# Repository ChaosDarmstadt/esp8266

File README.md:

Fun projects with ESP8266 IoT chip

## ESPLight

ESP8266 and WS2812 based, wifi enabled LED matrix.
What you need:

* 3.3V LDO TLV2217-33KCSE3
* 22uF Elko
* 0.1uF
* 5V 4A with barrel connector
* 5,5/2,5 mm barrel
* WS2812 rgb LED 60 px/m
* spacer bolt + screws M3 10mm
* 6x Push Button
* 10k resistor 1/4W
* ESP8266 ESP-07
* Stuff for manufacturing the PCB
* 2x 12cm x 26cm x 3mm translucent acrylic glass
* 3.3V TTL FTDI for flashing NodeMCU and nodemcu uploader for lua scripts

(AliExpress, Bauhaus, Pollin)

### related links
[send text over wifi](https://github.com/Nervengift/esplight.py)
[nodemcu](https://github.com/nodemcu/nodemcu-firmware)
[basic howto](https://wiki.chaos-darmstadt.de/wiki/ESP8266)

## ESPBreakout
ESP8266 Breakout Board

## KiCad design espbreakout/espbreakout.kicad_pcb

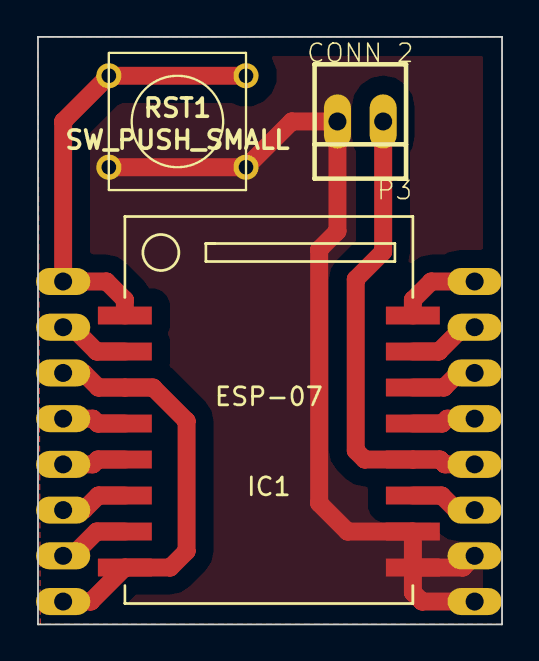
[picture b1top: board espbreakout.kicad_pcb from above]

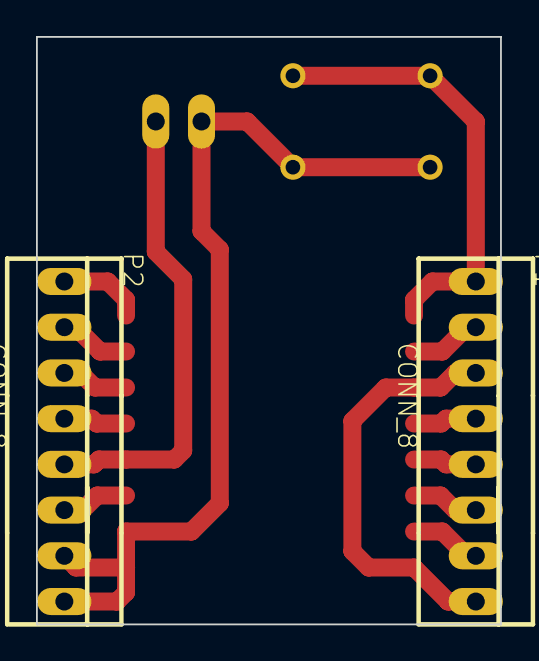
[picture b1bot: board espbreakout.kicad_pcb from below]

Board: 2 copper layers, 25.8 x 32.6 mm, 5 parts (2 on the bottom side), 14 nets.

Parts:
IC1: ESP-07; ESP-07v2
P1, P2: CONN_8; PINHEAD1-8
P3: CONN_2; PINHEAD1-2
RST1: SW_PUSH_SMALL

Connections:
+3.3V: IC1.3, IC1.8, P1.3, P1.8
GND: IC1.9, IC1.10, P2.7, P2.8, P3.2, RST1.2
unnamed: IC1.11, P2.6
unnamed: IC1.13, P2.4
unnamed: IC1.14, P2.3
unnamed: IC1.15, P2.2
unnamed: IC1.16, P2.1
unnamed: IC1.1, P1.1, RST1.1
unnamed: IC1.2, P1.2
unnamed: IC1.4, P1.4
unnamed: IC1.5, P1.5
unnamed: IC1.6, P1.6
unnamed: IC1.7, P1.7
unnamed: IC1.12, P2.5, P3.1

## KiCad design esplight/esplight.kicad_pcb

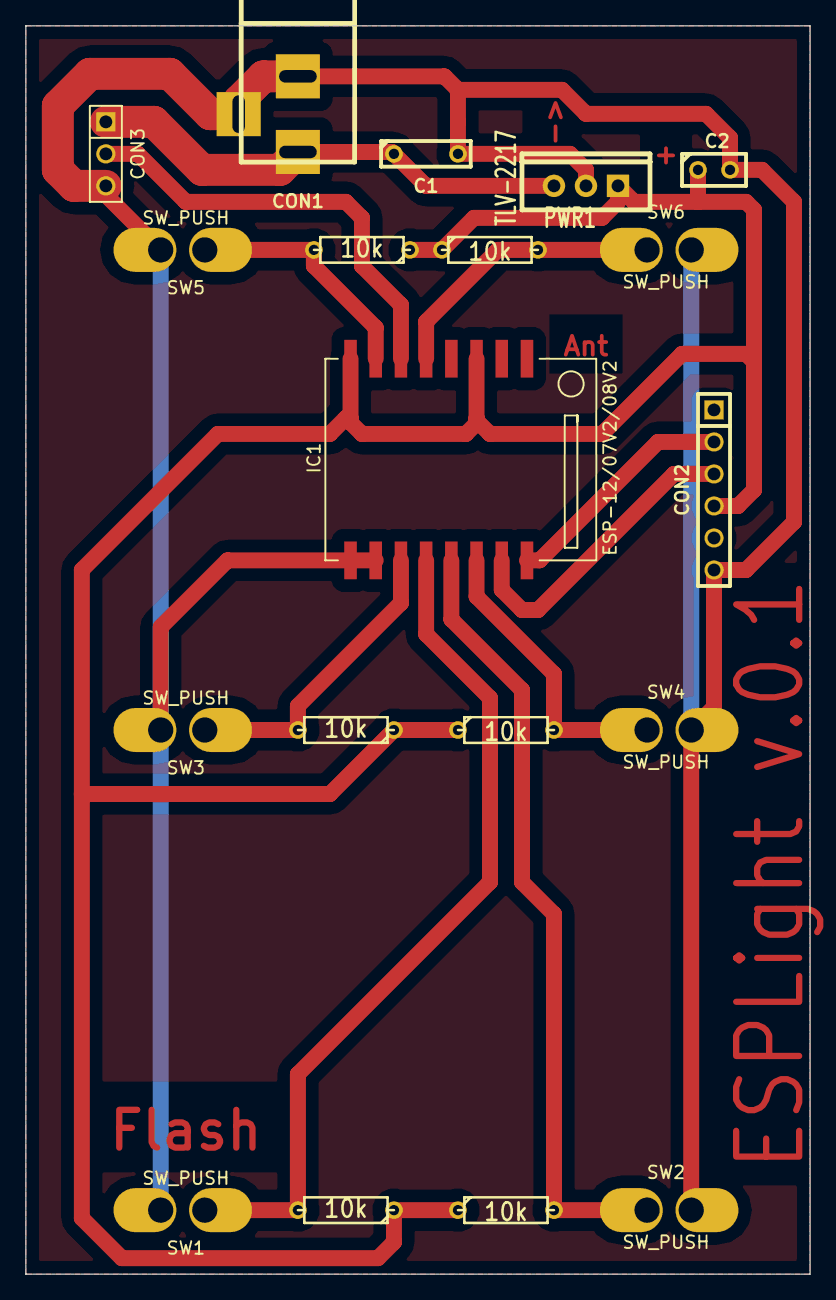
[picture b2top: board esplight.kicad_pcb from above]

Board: 2 copper layers, 62.2 x 99.1 mm, 19 parts (0 on the bottom side), 12 nets.

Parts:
C1: 0.1u; C2
C2: 22u; C1
CON1: BARREL_JACK
CON2: CONN_FTDI; PIN_ARRAY-6X1
CON3: CONN_WS2812; PIN_ARRAY_3X1
IC1: ESP-12/07V2/08V2; ESP-07v2
PWR1: TLV-2217; TO220_VERT
R1, R2, R3, R4, R5, R6: 10k; R3
SW1, SW2, SW3, SW4, SW5, SW6: SW_PUSH; PBS-10

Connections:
+3.3V: C2.1, CON2.4, IC1.3, IC1.8, PWR1.1, R1.1, R2.1, R3.1, R4.1, R5.1, R6.1
GND: C1.2, C2.2, CON1.2, CON1.3, CON2.6, CON3.3, IC1.9, IC1.10, PWR1.3, SW1.1, SW2.1, SW3.1, SW4.1, SW5.1, SW6.1
unnamed: IC1.14, R4.2, SW4.2
unnamed: IC1.7, R5.2, SW5.2
unnamed: IC1.5, R6.2, SW6.2
unnamed: CON3.2, IC1.6
unnamed: IC1.11, R3.2, SW3.2
unnamed: IC1.13, R2.2, SW2.2
unnamed: IC1.12, R1.2, SW1.2
unnamed: CON2.3, IC1.15
unnamed: CON2.2, IC1.16
VCC: C1.1, CON1.1, CON3.1, PWR1.2

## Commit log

2015-05-25 add parts list
2015-05-25 add ESPLight image
